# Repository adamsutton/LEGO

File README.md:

LEGO Models
===============================================================================
(c) 2017 Adam Sutton

Intro
-----

This repository contains a bunch of Lego models (mostly official ones) that I
have and have built and/or animated.

The LXF models are for the most part NOT my own work and have been found on the
web. I do not pretend any ownership and they are only kept here for convenience and in case I need to make alterations for the purpose of animation.

Some of the models have been lit / animated and this repository contains any electronics designs (schematics, PCBs) and firmware used for the job.

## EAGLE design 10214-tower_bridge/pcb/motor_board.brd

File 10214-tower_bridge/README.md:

10214 Tower Bridge
==================

This is my first endeavour at lighting and animating my LEGO models. The plan
was to motorise both halves of the bridge and to add lots of LEDs to the main structure.

This was also my first electronics project, so tried to keep things fairly simple. Originally the intention was just to build something out of veriboard or similar, but a friend showed my how easy it was to design and schematic / PCB and get it fabricated for minimal cost.

Mechanics
---------

The design has 2 stepper motors, one for each half of the bridge. These are hidden away under the road section of each tower. Some minor re-arrangement of the internal structure was needed to make space and also additional brick work was added to hold the motors in place.

I also removed the original pivots as they weren't designed to be moved automatically and presented too much friction. A simple technic bar and end plugs was used to replce this. Some standard bricks were also replaced with technic (holed) bricks to allow wires to run.

Each stepper had a technic circular disc pushed onto the spindle to help guide the winding of the cable.

Electronics
-----------

A simple PCB comprising an arduino, darlington array (to provide 5V signals to the motor), connectors for sensors, tower interconnect, motor and LEDs and 220ohm resistor for each LED (I didn't do a proper job and match, it's good enough).

There is also a string of LEDs in the top of the bridge crossing between the two towers. These have inline resistors as it I didn't want to have to run lots of cables from the PCB!

The two boards are then interconnected by a 3-wire cable carrying GND, VCC (5v) and RX (RS232). The serial RX acts as a receive only "bus", allowing me to address both towers simultaneously. There is no feedback, but none was required.

The interconnect header on one tower also doubles up as the means of external connection to the power supply and control board (an rpi).

Firmware
--------

The easy bit :) although as usual being software I ended up over-engineering and eventually scrapped lots of it to keep things simple.

The arduino monitors the end stop sensors and controls the bridge autonomously. It has the option to move to top, bottom or a specific position (based on stepper steps).

There is also individual control of most of the LEDs (total overkill, but I had lots of spare IO, so what the heck). The only ones that aren't individually controllable are the ones spanning the two bridges.

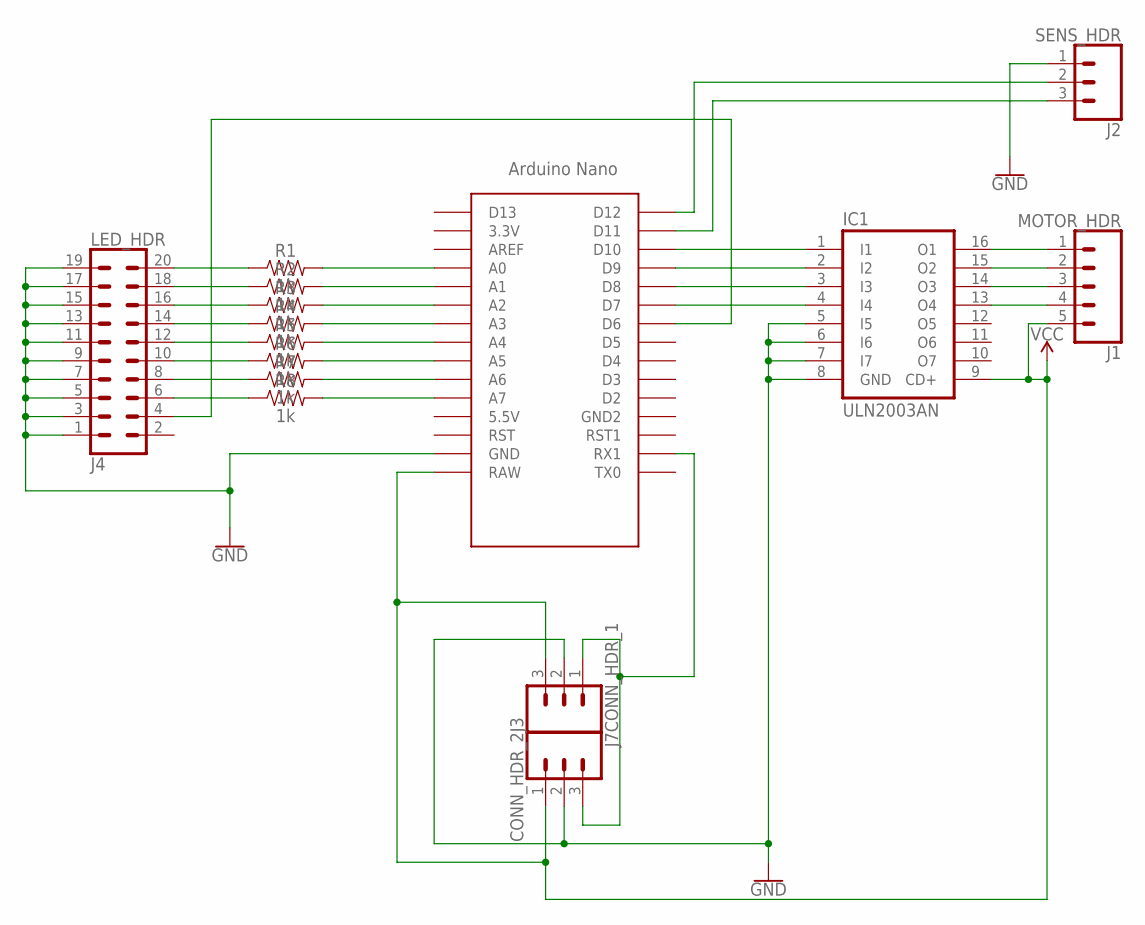
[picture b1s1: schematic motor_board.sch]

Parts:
IC1: ULN2003AN; DIL16
J1: MOTOR_HDR; 1X05
J2: SENS_HDR; 1X03
J3: CONN_HDR_1; 1X03
J4: LED_HDR; 2X10
J7: CONN_HDR_2; 1X03
R1, R2, R3, R4, R5, R6, R7, R8: 1k; AXIAL-0.3
U$1: NANO

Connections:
DOWN_DET: J2.3, U$1.D11
GND: IC1.5 (I5), IC1.6 (I6), IC1.7 (I7), IC1.8 (GND), J2.1, J3.2, J4.1, J4.3, J4.5, J4.7, J4.9, J4.11, J4.13, J4.15, J4.17, J4.19, J7.2, U$1.GND
LED1: R1.P$2 (2), U$1.A0
LED2: R2.P$2 (2), U$1.A1
LED3: R3.P$2 (2), U$1.A2
LED4: R4.P$2 (2), U$1.A3
LED5: R5.P$2 (2), U$1.A4
LED6: R6.P$2 (2), U$1.A5
LED7: R7.P$2 (2), U$1.A6
LED8: R8.P$2 (2), U$1.A7
unnamed: IC1.1 (I1), U$1.D10
unnamed: IC1.2 (I2), U$1.D9
unnamed: IC1.3 (I3), U$1.D8
unnamed: IC1.4 (I4), U$1.D7
unnamed: IC1.16 (O1), J1.1
unnamed: IC1.15 (O2), J1.2
unnamed: IC1.14 (O3), J1.3
unnamed: IC1.13 (O4), J1.4
unnamed: J4.20, R1.P$1 (1)
unnamed: J4.18, R2.P$1 (1)
unnamed: J4.16, R3.P$1 (1)
unnamed: J4.14, R4.P$1 (1)
unnamed: J4.4, U$1.D6
unnamed: J4.12, R5.P$1 (1)
unnamed: J4.10, R6.P$1 (1)
unnamed: J4.8, R7.P$1 (1)
unnamed: J4.6, R8.P$1 (1)
RX: J3.1, J7.3, U$1.RX1
UP_DET: J2.2, U$1.D12
VCC: IC1.9 (CD+), J1.5, J3.3, J7.1, U$1.RAW

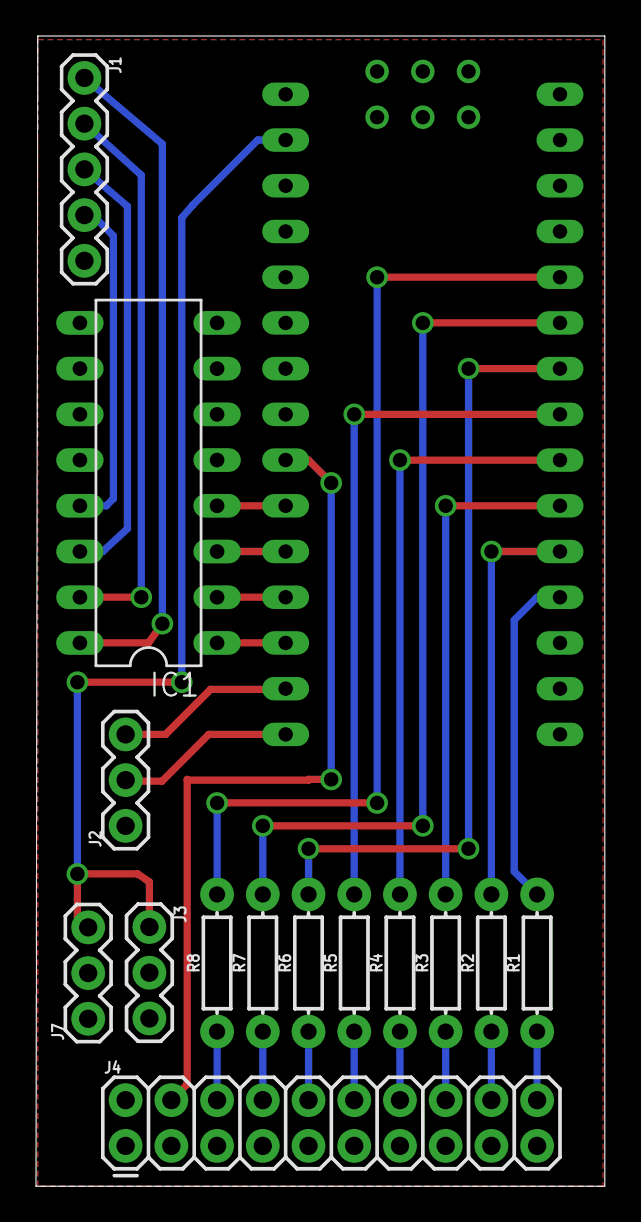
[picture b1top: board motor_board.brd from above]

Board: 2 copper layers, 31.6 x 63.9 mm, 15 parts (0 on the bottom side), 30 nets.

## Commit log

2017-01-28 towerbridge: added PCB and schematic
    There are some minor errors (and redundancies) in this, but it's the version
    that got printed.
2017-01-28 docs: added simple README
2017-01-28 models: initial import of LXF models
2017-01-28 towerbridge: added initial cut at firmware
    Some of this stuff needs moving to more generic location / library and some of
    it really needs tidying up.
2017-01-28 towerbridge: added README

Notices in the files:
parts and their libraries:
SparkFun-Connectors: Licensing: Creative Commons ShareAlike 4.0 International - https://creativecommons.org/licenses/by-sa/4.0
